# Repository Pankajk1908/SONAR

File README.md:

# SONAR Device – End-to-End Hardware Design

🚀 **SONAR Device** is a complete **hardware design project** showcasing the design, iteration, and integration of a **SONAR-based sensing system**, including schematics and multi-revision PCB layouts.

This project demonstrates hands-on expertise in **analog & digital electronics, PCB design, and system-level hardware development**.

---

## 🔍 Project Summary

- **Domain:** Embedded Systems / Electronics / Sensors
- **Focus:** SONAR transmitter, signal processing, and PCB integration
- **Outcome:** Fabrication-ready PCB designs with multiple iterations
- **Tools Used:** Autodesk EAGLE, PCB CAD workflows

---

## 🎯 Problem Statement

Design a **reliable SONAR sensing hardware system** capable of:
- Generating transmission signals
- Handling received echoes with minimal noise
- Integrating transmitter and signal conditioning on a compact PCB

---

## 🧠 Solution Approach

The project was developed through **iterative hardware refinement**:

1. **Initial schematic & PCB**
2. Dedicated **transmitter (TX) design**
3. **Signal-to-Noise Ratio (SNR)** optimization board
4. **Final integrated full-board design**
5. Alternate revisions for layout optimization

This approach mirrors **real-world hardware product development cycles**.

---

## 📁 Repository Structure

```

SONAR/
│
├── PCB.brd / PCB.sch               # Initial design
├── PCB_NEW_Tx.brd / .sch            # Improved TX circuit
├── PCB_tx_snr.brd / .sch            # TX + SNR optimization
├── pcb_full.brd / pcb_full.sch      # Final integrated PCB
├── pcb_full_1.brd / pcb_full_1.sch  # Alternate revision
└── README.md

````

---

## 🛠️ Technical Skills Demonstrated

### 🔌 Electronics & Hardware
- SONAR circuit design
- Analog signal conditioning
- Noise reduction and SNR considerations
- Power routing & grounding strategies

### 🧩 PCB Design
- Multi-layer PCB layout
- Component placement optimization
- Routing for signal integrity
- Iterative design revisions

### 🧪 Engineering Practices
- Design iteration & validation
- Modular hardware architecture
- Fabrication-ready outputs

---

## ⚙️ Tools & Technologies

| Category | Tools |
|--------|------|
| PCB Design | Autodesk EAGLE |
| File Types | `.sch`, `.brd` |
| Hardware | SONAR transmitter & receiver circuitry |
| Workflow | Schematic → PCB → Revision → Integration |

---

## ▶️ How to Explore the Project

### 1️⃣ Clone the Repository
```bash
git clone https://github.com/Pankajk1908/SONAR.git
cd SONAR
````

### 2️⃣ Open Design Files

* Open `.sch` files for schematics
* Open `.brd` files for PCB layouts
* Use **Autodesk EAGLE** or compatible tools

### 3️⃣ Review Design Decisions

* Compare revisions to see improvements
* Analyze TX vs SNR-focused boards
* Study final board integration

---

## 📈 Key Learnings

* Translating system requirements into hardware
* Iterative PCB refinement based on performance goals
* Managing trade-offs between size, noise, and complexity
* End-to-end ownership of a hardware design lifecycle

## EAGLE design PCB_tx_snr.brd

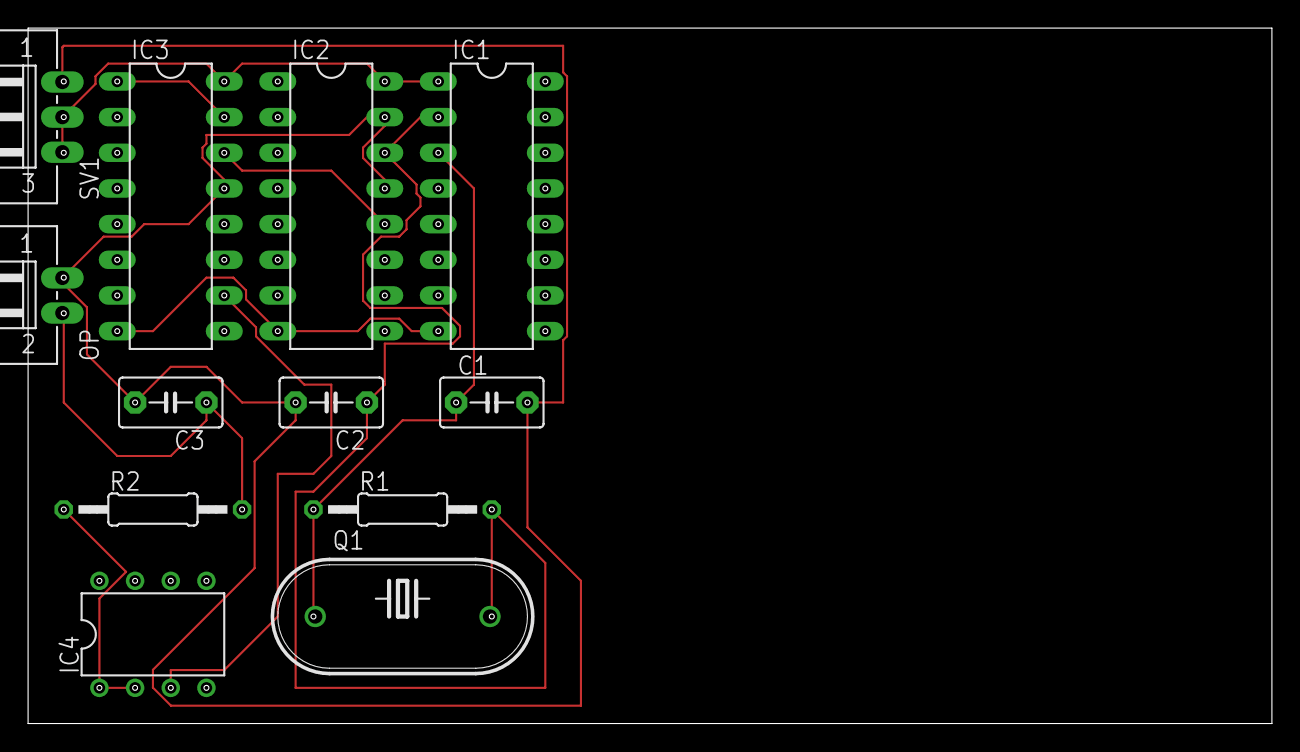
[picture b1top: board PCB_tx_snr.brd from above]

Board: 2 copper layers, 88.6 x 49.5 mm, 12 parts (0 on the bottom side), 10 nets.

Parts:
C1, C2, C3: C5B3.5
IC1: 4049N; DIL16
IC2, IC3: 4017N; DIL16
IC4: TL072P; DIL08
OP: L02P
Q1: HC33U-V
R1, R2: 0207/12
SV1: L03P

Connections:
GND: C1.2, C2.2, C3.2, IC2.13, IC2.15, IC3.13, OP.1, SV1.1
unnamed: C1.1, IC1.3, Q1.1, R1.1
unnamed: C2.1, IC1.2, IC2.14, Q1.2, R1.2
unnamed: C3.1, OP.2, R2.2
unnamed: IC3.1, IC3.15
unnamed: IC3.10, IC4.3
unnamed: IC4.1, IC4.2, R2.1
unnamed: IC2.12, IC3.14
VDD: IC1.1, IC2.16, IC3.16, SV1.2, SV1.3
VSS: IC1.8, IC2.8, IC3.8

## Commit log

2025-12-14 Add README for SONAR Device hardware design project
    Added detailed project documentation for SONAR device including project summary, problem statement, solution approach, repository structure, technical skills, tools, and exploration instructions.
